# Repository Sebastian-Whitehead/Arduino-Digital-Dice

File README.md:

# DIY Digital Dice (d10000)

​	This is an Arduino based DIY digital dice that, as standard, can generate a random number between 0 and 4 /6 /8 /10 /12 /20 /100 /1000 *or* 10000 along with a coin flip between heads and tails (1/2.) Using a gyroscope the device can sense its rotational acceleration around any one of the three axis and generate a random number when a specified threshold is reached. Originally created to use along side with an extended 'chaos magic' in DnD 5e. Despite this the dice can function as a physical random number generator for any situation with little modification to the Arduino code if wanted.

### Prerequisites

###### Software:

- Access to a 3d printer (... *cm* x ... *cm* x ... *cm*  **min print size**) and slicer
- 3D modelling program *(Fusion 360)*
- Arduino IDE *(or other Arduino compatible IDE's)*
  - LiquidCrystal.h
  - Wire.h
- EDA software Autodesk 'Eagle' *(alternatively 'Easy EDA')*

###### Components [Standard]:

- Arduino Nano
- 8x2 liquid crystal display
- MPU-6050 Gyroscope
- 2x 10k Resistor *THT*
- 1x 10k potentiometer 
- 2x 100nF non polarized capacitor (5.8mm *THT*) 
- 1x Speaker
- 2x Momentary Buttons <u>[hole mountable]</u> 
- 1x Toggle Switch / Button <u>[hole mountable]</u> 
- 1x 1s rechargeable Lithium Polymer battery and USB charging circuit 
  *<u>(Easily found from butchering a 5v battery charger)</u>*
- 1x PCB (*see production files*)
- 1x 3D printed shell
- (screws, nuts and washers) ...

### Contributing

All contributions are accepted with no requirements for permission from authors.

### Version

Release 0.1 **[Board Design & Program]** (08.03.2020)

### Authors

- **Sebastian Whitehead** - *Initial work* [*Version 1.0*]

### License

This Project is licensed under the MIT License - See the LICENSE.md file for details

### Acknowledgments

-  Dejan - howtomechatronics.com - parts of the Gyroscope code

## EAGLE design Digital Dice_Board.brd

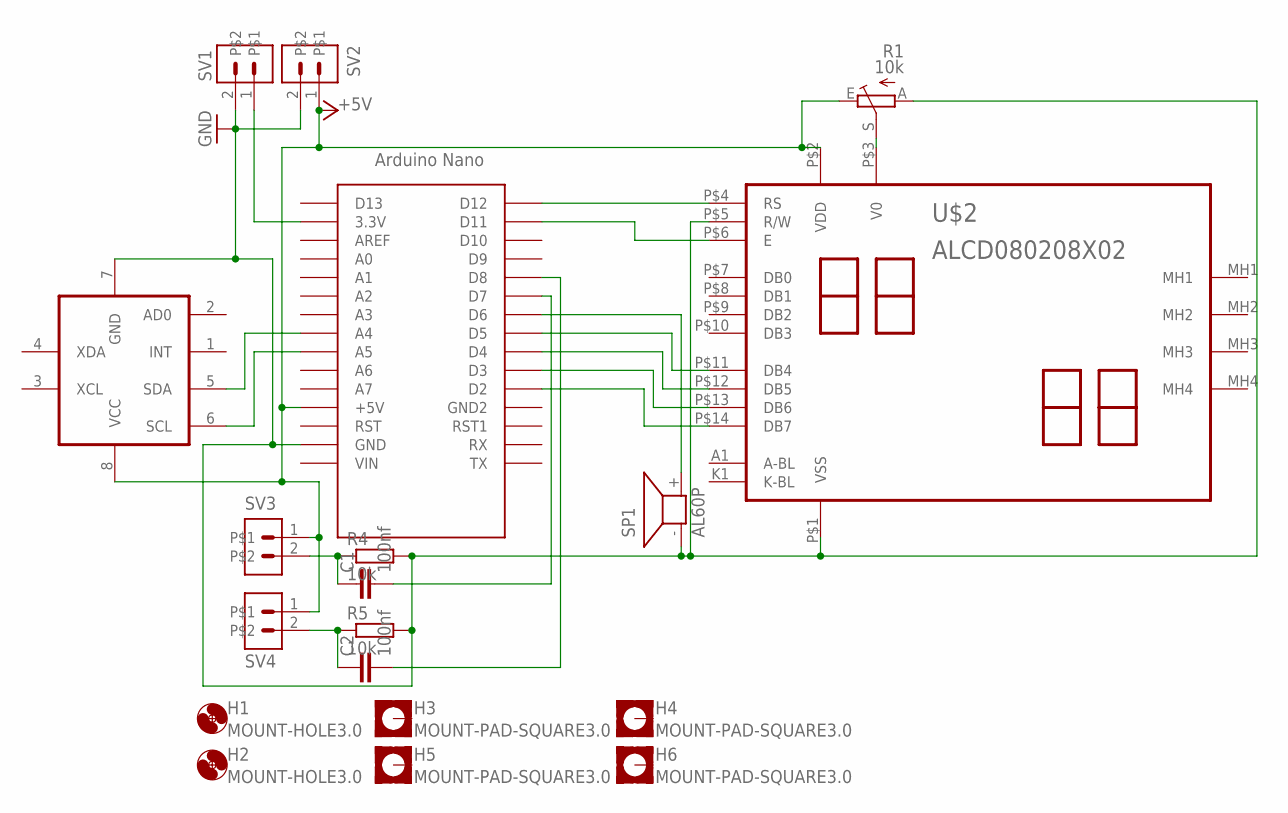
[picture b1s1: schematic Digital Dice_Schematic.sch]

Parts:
C1, C2: 100nf; C050-025X075W
H1, H2: MOUNT-HOLE3.0; 3,0
H3, H4, H5, H6: MOUNT-PAD-SQUARE3.0; 3,0-PAD-SQUARE
R1: 10k; CA9V
R4, R5: 10k; 0207/12
SP1: AL60P
SV1, SV2, SV3, SV4: MA02-1
U$1: NANO
U$2: ALCD080208X02; ALCD0802
X1: GYRO_MPU-6050; MPU

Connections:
+5V: R1.E, SV2.1, SV3.1, SV4.1, U$1.5V (+5V), U$2.P$2 (VDD), X1.8 (VCC)
GND: R1.A, R4.2, R5.2, SP1.- (1), SV1.2, SV2.2, U$1.GND, U$2.P$1 (VSS), U$2.P$5 (R/W), X1.7 (GND)
unnamed: U$1.D12, U$2.P$4 (RS)
unnamed: C2.1, R5.1, SV4.2
unnamed: U$1.A5, X1.6 (SCL)
unnamed: U$1.A4, X1.5 (SDA)
unnamed: R1.S, U$2.P$3 (V0)
unnamed: SV1.1, U$1.3.3V
unnamed: C1.1, R4.1, SV3.2
unnamed: U$1.D11, U$2.P$6 (E)
unnamed: U$1.D5, U$2.P$11 (DB4)
unnamed: U$1.D4, U$2.P$12 (DB5)
unnamed: U$1.D3, U$2.P$13 (DB6)
unnamed: U$1.D2, U$2.P$14 (DB7)
unnamed: SP1.+ (2), U$1.D6
unnamed: C1.2, U$1.D7
unnamed: C2.2, U$1.D8

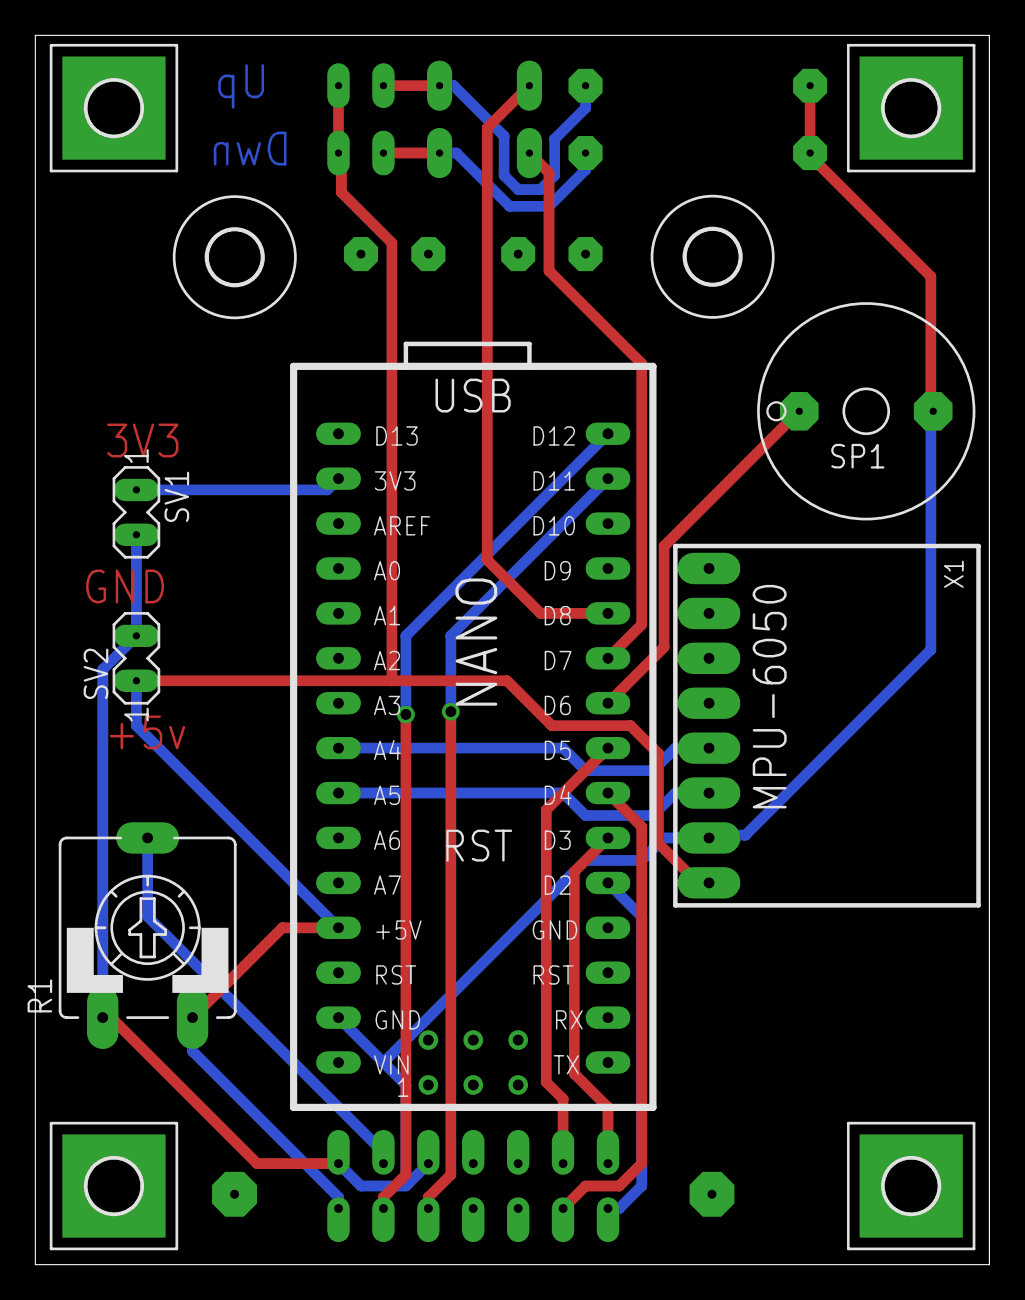
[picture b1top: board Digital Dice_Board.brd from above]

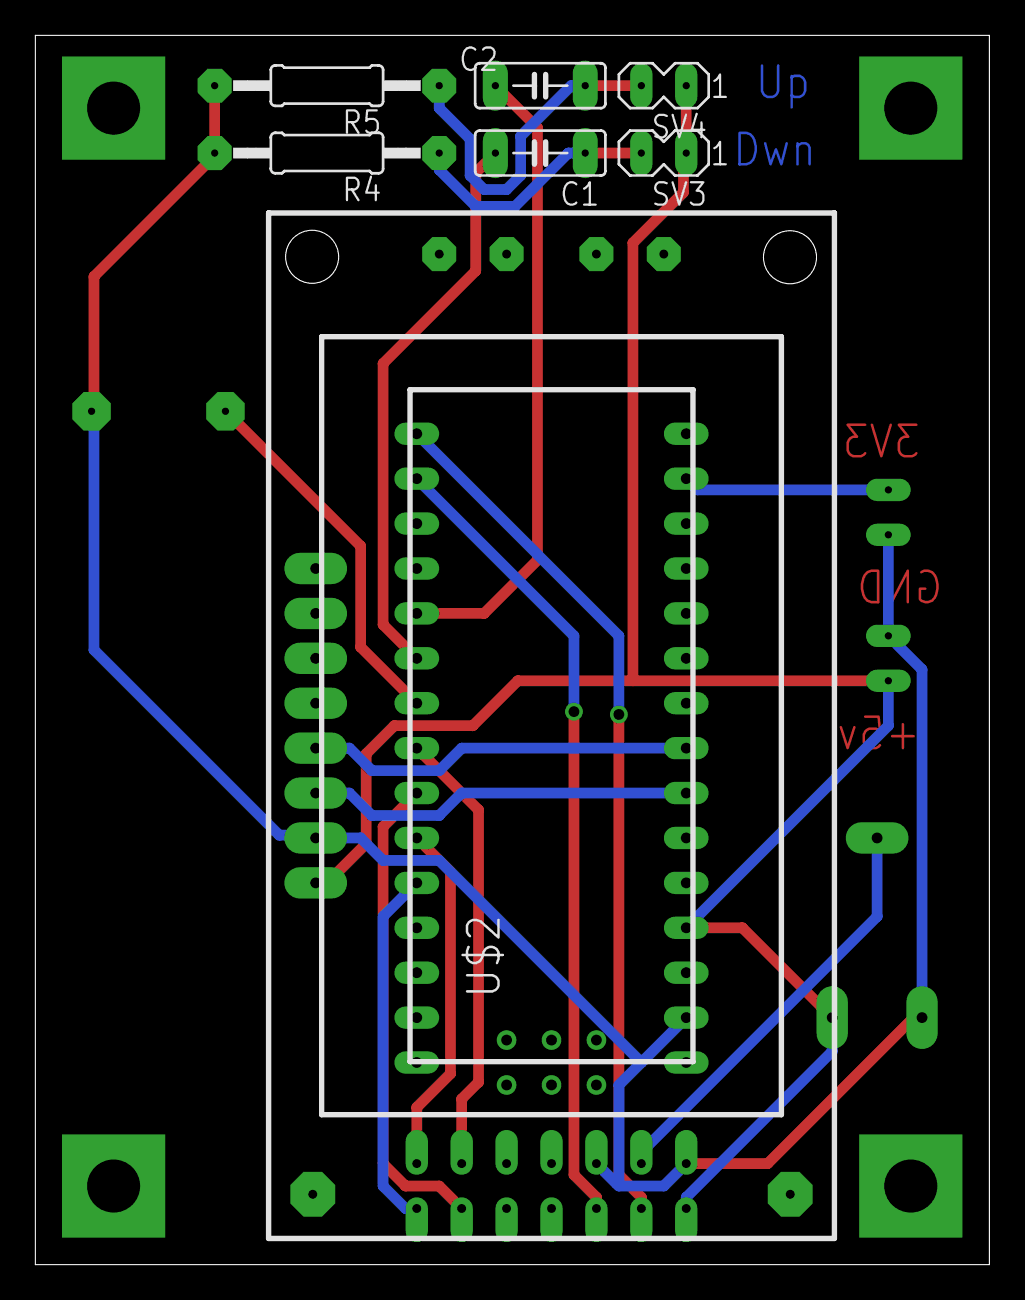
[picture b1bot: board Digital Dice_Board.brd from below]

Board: 2 copper layers, 54.0 x 69.5 mm, 19 parts (7 on the bottom side), 17 nets.

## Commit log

2020-03-08 Version 0.1
    Version 0.1 release of the program with both the curcuit design; PCB schematic; arduino program and assembly instructions.
